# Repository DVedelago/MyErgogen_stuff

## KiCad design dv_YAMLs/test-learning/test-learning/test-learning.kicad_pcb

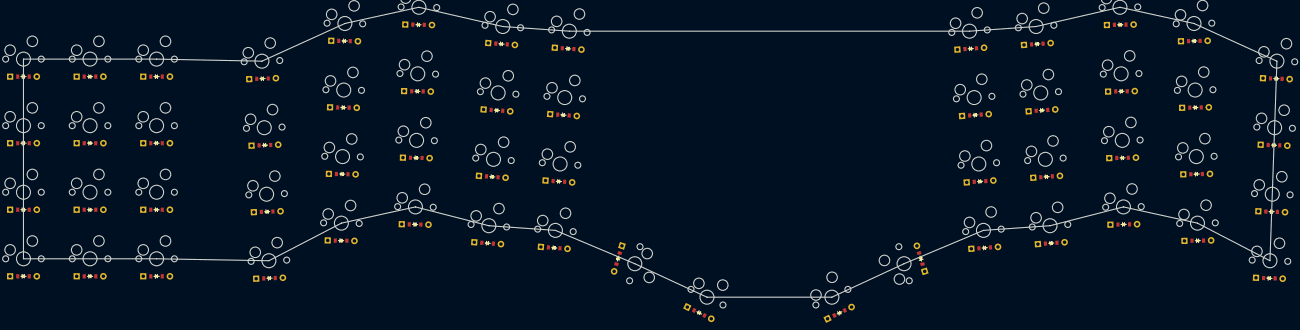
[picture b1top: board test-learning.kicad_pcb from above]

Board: 2 copper layers, 357.8 x 82.8 mm, 112 parts (0 on the bottom side), 56 nets, no tracks yet.

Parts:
D1, D2, D3, D4, D5, D6, D7, D8, D9, D10, D11, D12, D13, D14, D15, D16, D17, D18, D19, D20, D21, D22, D23, D24, D25, D26, D27, D28, D29, D30, D31, D32, D33, D34, D35, D36, D37, D38, D39, D40, D41, D42, D43, D44, D45, D46, D47, D48, D49, D50, D51, D52, D53, D54, D55, D56: ComboDiode
S1, S2, S3, S4, S5, S6, S7, S8, S9, S10, S11, S12, S13, S14, S15, S16, S17, S18, S19, S20, S21, S22, S23, S24, S25, S26, S27, S28, S29, S30, S31, S32, S33, S34, S35, S36, S37, S38, S39, S40, S41, S42, S43, S44, S45, S46, S47, S48, S49, S50, S51, S52, S53, S54, S55, S56: MX

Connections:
C1_R1: D45.2, S45.2
C1_R2: D46.2, S46.2
C1_R3: D47.2, S47.2
C1_R4: D48.2, S48.2
C2_R1: D49.2, S49.2
C2_R2: D50.2, S50.2
C2_R3: D51.2, S51.2
C2_R4: D52.2, S52.2
C3_R1: D53.2, S53.2
C3_R2: D54.2, S54.2
C3_R3: D55.2, S55.2
C3_R4: D56.2, S56.2
disazio_fan: D42.2, S42.2
index_alpha1: D13.2, S13.2
index_alpha2: D14.2, S14.2
index_alpha3: D15.2, S15.2
index_mod: D16.2, S16.2
index_stretch_alpha1: D17.2, S17.2
index_stretch_alpha2: D18.2, S18.2
index_stretch_alpha3: D19.2, S19.2
index_stretch_mod: D20.2, S20.2
middle_alpha1: D9.2, S9.2
middle_alpha2: D10.2, S10.2
middle_alpha3: D11.2, S11.2
middle_mod: D12.2, S12.2
mirror_disazio_fan: D44.2, S44.2
mirror_index_alpha1: D33.2, S33.2
mirror_index_alpha2: D34.2, S34.2
mirror_index_alpha3: D35.2, S35.2
mirror_index_mod: D36.2, S36.2
mirror_index_stretch_alpha1: D37.2, S37.2
mirror_index_stretch_alpha2: D38.2, S38.2
mirror_index_stretch_alpha3: D39.2, S39.2
mirror_index_stretch_mod: D40.2, S40.2
mirror_middle_alpha1: D29.2, S29.2
mirror_middle_alpha2: D30.2, S30.2
mirror_middle_alpha3: D31.2, S31.2
mirror_middle_mod: D32.2, S32.2
mirror_pinky_alpha1: D21.2, S21.2
mirror_pinky_alpha2: D22.2, S22.2
mirror_pinky_alpha3: D23.2, S23.2
mirror_pinky_mod: D24.2, S24.2
mirror_ring_alpha1: D25.2, S25.2
mirror_ring_alpha2: D26.2, S26.2
mirror_ring_alpha3: D27.2, S27.2
mirror_ring_mod: D28.2, S28.2
mirror_spazio_fan: D43.2, S43.2
pinky_alpha1: D1.2, S1.2
pinky_alpha2: D2.2, S2.2
pinky_alpha3: D3.2, S3.2
pinky_mod: D4.2, S4.2
ring_alpha1: D5.2, S5.2
ring_alpha2: D6.2, S6.2
ring_alpha3: D7.2, S7.2
ring_mod: D8.2, S8.2
spazio_fan: D41.2, S41.2

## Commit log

2025-08-13 frst commit and first YAML test
2025-08-13 folder struct
2025-08-14 outline defined.
2025-08-17 TODO: move vertices
2025-08-18 revised board outline
2025-08-18 re-revised outline - fixed stuff
2025-08-20 definitive outline, maybe
2025-08-29 new commit, modified board outline
2025-09-11 new ortholinear keeb
